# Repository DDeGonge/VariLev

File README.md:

# VariLev
Heckin smart magnetic levitation base

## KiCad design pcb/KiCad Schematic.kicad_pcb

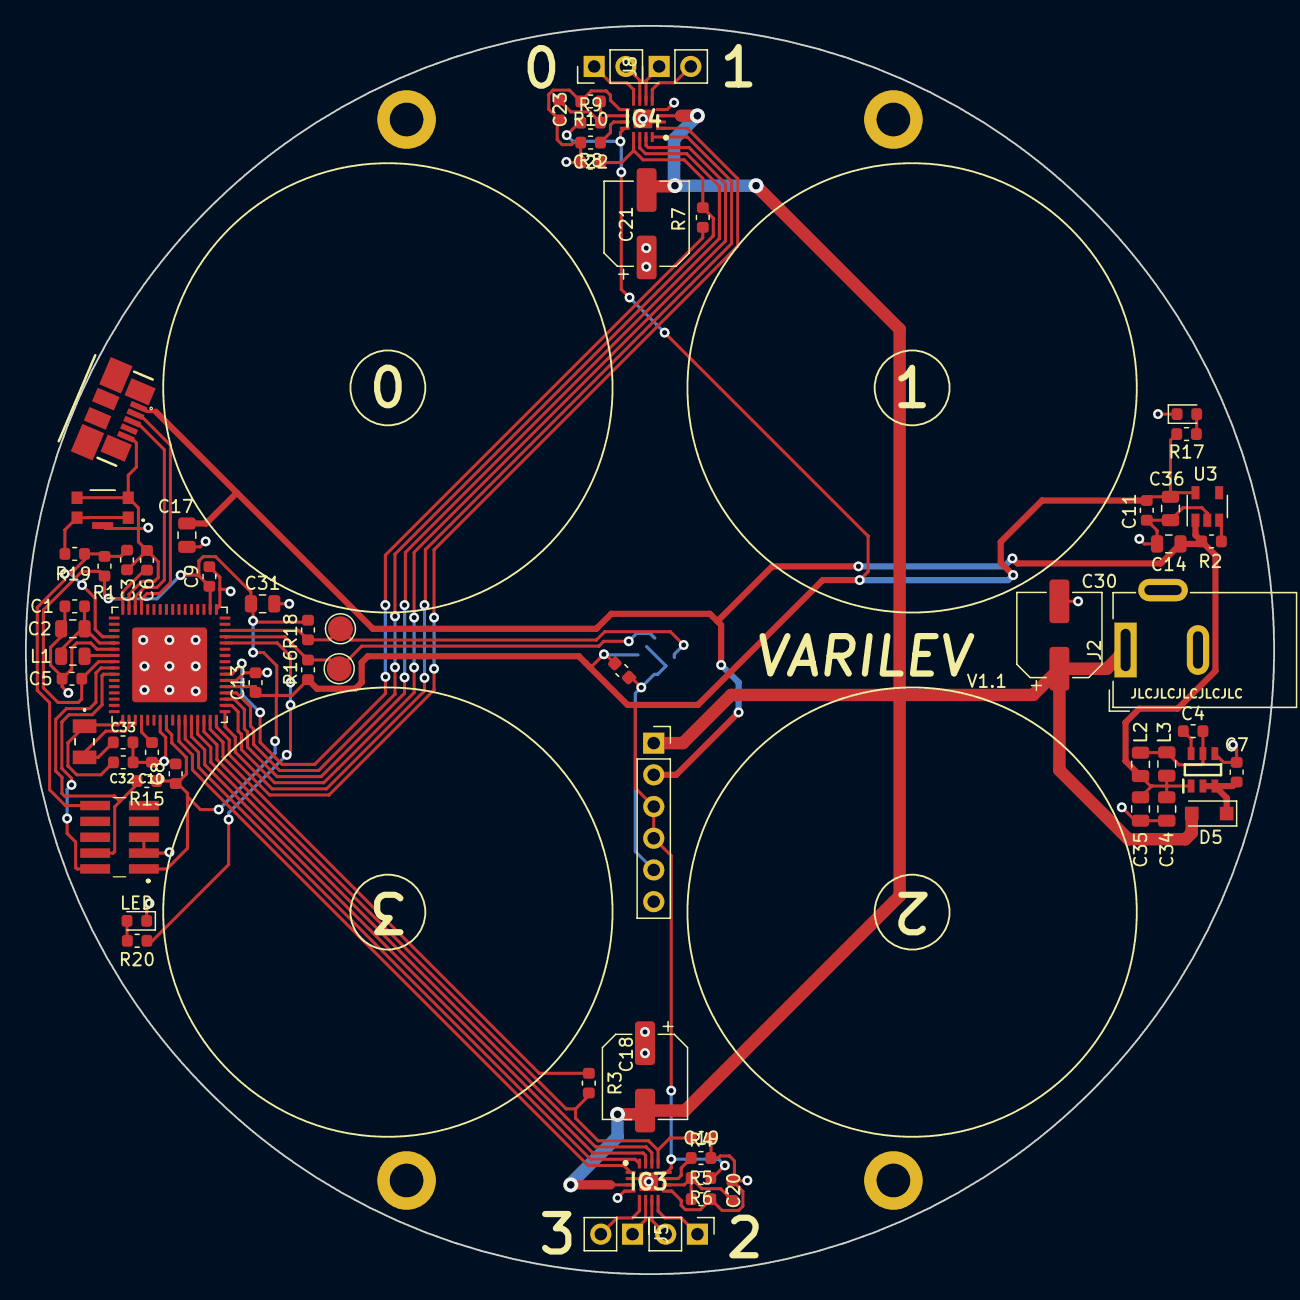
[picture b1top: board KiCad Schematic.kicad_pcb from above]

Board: 2 copper layers, 100.0 x 100.0 mm, 72 parts (1 on the bottom side), 48 nets.

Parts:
C1, C4, C5, C6, C8, C9, C12, C13, C20, C23: 100nF; C_0603_1608Metric
C2, C14, C17, C31, C34, C35, C36: 10uF; C_0805_2012Metric
C3, C7, C10, C11: 1uF; C_0603_1608Metric
C18, C21, C30: 47uF; CP_Elec_6.3x7.7
C19, C22: 22nF; C_0603_1608Metric
C32, C33: 22pF; C_0603_1608Metric
D1, D2: LED; LED_0603_1608Metric
D5: CGRTS4004-HF; D_SOD-123F
IC1: AP63205WU-7; SOT95P280X100-6N
IC2: ATSAMD51J19A-MU; QFN-64-1EP_9x9mm_P0.5mm_EP6x6mm
IC3, IC4: TC78H660FTG,EL; QFN50P300X300X90-17N
J1, J4: PAD; TestPoint_Pad_D2.0mm
J2: Conn_01x02; BarrelJack_Wuerth_6941xx301002
J3: 47346-0001
J5, J7, J8, J9: Conn_01x02; PinHeader_1x02_P2.54mm_Vertical
J6: 20021121-00010C4LF; 2002112100010C4LF
J17, J18, J19, J20: Hole; MountingHole_2.7mm_M2.5_DIN965_Pad
J22: Conn_01x06; PinSocket_1x06_P2.54mm_Vertical
L1, L2, L3: 10uH; L_0805_2012Metric
R1, R2, R3, R5, R6, R7, R9, R10, R15, R16, R18: 10k; R_0603_1608Metric
R4, R8: 75k; R_0603_1608Metric
R17, R19, R20: 174; R_0603_1608Metric
S1: KMR243GLFG; KMR421GULCLFS
U1: TLV493D; SOT-23-6
U3: AP2112K-3.3; SOT-23-5
Y1: LFXTAL009678REEL

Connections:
+3V3: C5.1, C6.1, C8.1, C9.1, C11.1, C12.1, C13.1, C31.1, C36.1, IC2.8, IC2.21, IC2.34, IC2.48, IC2.56, IC3.12, IC4.12, J6.1, J22.3, J22.4, R1.1, R5.1, R9.1, R15.1, R16.1, R17.2, R18.1, U1.4, U3.5
+5V: C14.1, C17.1, C34.1, C35.1, IC1.1, J3.1, J22.2, L2.1, L3.1, R2.1, U3.1
+VDC: C18.2, C21.2, C30.1, D5.2, IC3.3, IC4.3, J2.1, J22.1
/AREF: C10.1, IC2.4
/D+: IC2.46, J3.3
/D-: IC2.45, J3.2
/GATE0: IC2.17, IC4.16
/GATE1: IC2.18, IC4.15
/GEN0: IC2.10, IC3.1
/GEN1: IC2.11, IC3.16
/GEN2: IC2.12, IC3.15
/GEN3: IC2.13, IC3.14
/GEN4: C19.1, IC2.14, IC3.13, R3.1
/GEN5: IC2.15, R3.2
/GEN6: IC2.16, IC4.1
/GEN7: IC2.19, IC4.14
/GEN8: C22.1, IC2.20, IC4.13, R7.1
/GEN9: IC2.23, R7.2
/GEN14: IC2.28, R20.2
/OSC0: C32.2, IC2.1, Y1.1
/OSC1: C33.1, IC2.2, Y1.2
/RESET: C3.1, IC2.52, J6.10, R1.2, R19.2
/SCL: IC2.30, J1.1, R18.2, U1.1
/SDA: IC2.29, J4.1, R16.2, U1.6
/SWCLK: IC2.57, J6.4, R15.2
/SWDIO: IC2.58, J6.2
/VDDCORE: C1.1, C2.1, IC2.53, L1.2
/VSW: IC2.55, L1.1
GND: C1.2, C2.2, C3.2, C5.2, C6.2, C7.2, C8.2, C9.2, C10.2, C11.2, C12.2, C13.2, C14.2, C17.2, C18.1, C19.2, C20.2, C21.1, C22.2, C23.2, C30.2, C31.2, C32.1, C33.2, C34.2, C35.2, C36.2, D1.1, D2.1, IC1.4, IC2.7, IC2.22, IC2.33, IC2.47, IC2.54, IC2.65, IC3.2, IC3.4, IC3.9, IC3.17, IC4.2, IC4.4, IC4.9, IC4.17, J2.2, J3.5, J6.3, J6.5, J17.1, J18.1, J19.1, J20.1, J22.5, J22.6, R4.2, R6.2, R8.2, R10.2, S1.2, S1.3, S1.5, U1.2, U1.3, U1.5, U3.2
unnamed: C4.1, IC1.5, L2.2, L3.2
unnamed: C4.2, IC1.6
unnamed: C7.1, D5.1, IC1.2, IC1.3
unnamed: C20.1, IC3.10, R5.2, R6.1
unnamed: C23.1, IC4.10, R9.2, R10.1
unnamed: D1.2, R17.1
unnamed: D2.2, R20.1
unnamed: IC3.5, J5.2
unnamed: IC3.6, J5.1
unnamed: IC3.7, J7.2
unnamed: IC3.8, J7.1
unnamed: IC3.11, R4.1
unnamed: IC4.5, J8.2
unnamed: IC4.6, J8.1
unnamed: IC4.7, J9.2
unnamed: IC4.8, J9.1
unnamed: IC4.11, R8.1
unnamed: R2.2, U3.3
unnamed: R19.1, S1.1, S1.4

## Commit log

2021-03-01 v1 pcb added
2021-03-18 add coil winder hardware, code that compiles (for now)
2021-07-25 update pcb to use h bridges and other stuff
2021-08-21 firmware stable but not fully working
2021-08-23 it kinda almost works
2021-09-09 final push, for now
